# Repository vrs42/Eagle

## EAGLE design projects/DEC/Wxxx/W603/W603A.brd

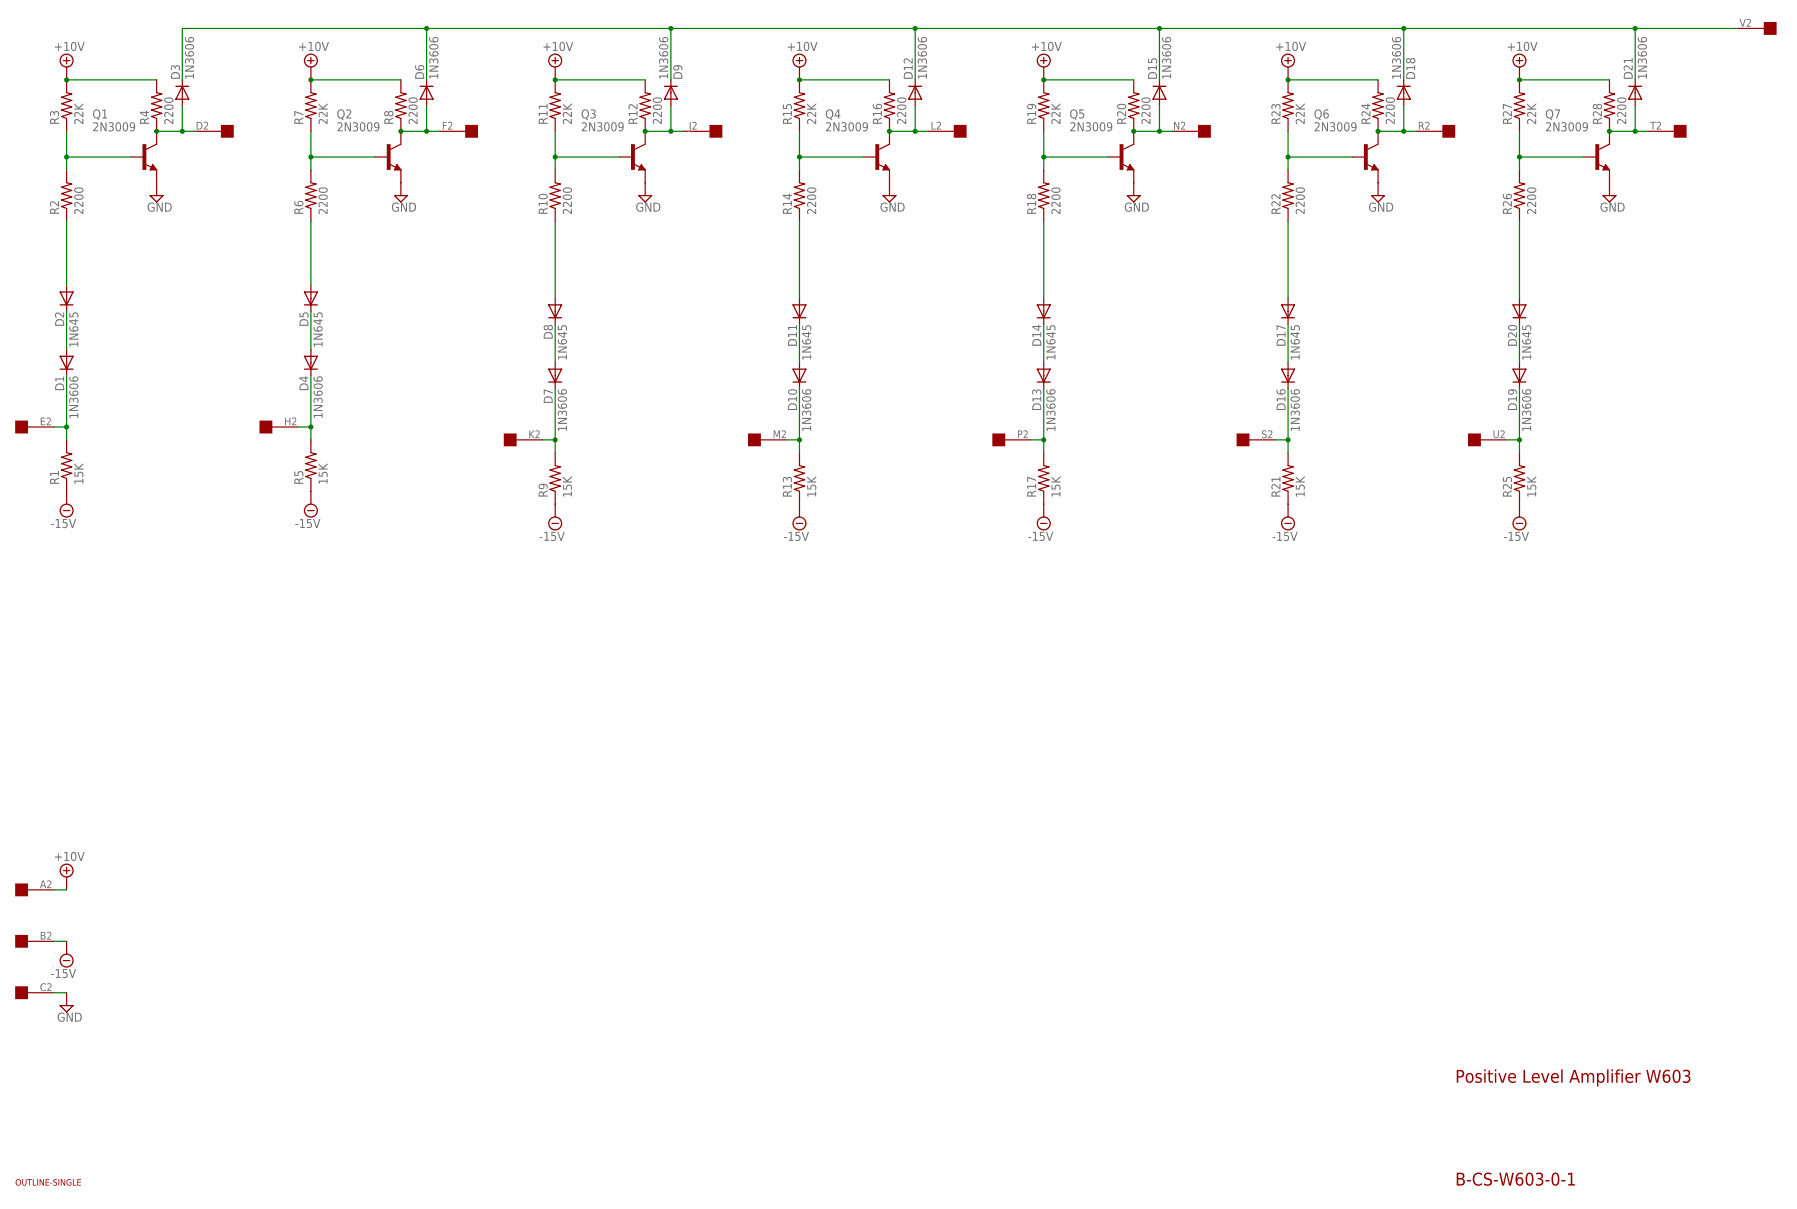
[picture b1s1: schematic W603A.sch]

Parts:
D1, D3, D4, D6, D7, D9, D10, D12, D13, D15, D16, D18, D19, D21: 1N3606; DO35-10
D2, D5, D8, D11, D14, D17, D20: 1N645; DO35-10
Q1, Q2, Q3, Q4, Q5, Q6, Q7: 2N3009; TO5
R1, R5, R9, R13, R17, R21, R25: 15K; 0207/10
R2, R4, R6, R8, R10, R12, R14, R16, R18, R20, R22, R24, R26, R28: 2200; 0207/10
R3, R7, R11, R15, R19, R23, R27: 22K; 0207/10
U$1: OUTLINE-SINGLE; SINGLE
U$2: EDGE-1; EDGE-CON1

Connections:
+10V: R3.2, R4.2, R7.2, R8.2, R11.2, R12.2, R15.2, R16.2, R19.2, R20.2, R23.2, R24.2, R27.2, R28.2, U$2.A2
-15V: R1.1, R5.1, R9.1, R13.1, R17.1, R21.1, R25.1, U$2.B2
GND: Q1.1 (E), Q2.1 (E), Q3.1 (E), Q4.1 (E), Q5.1 (E), Q6.1 (E), Q7.1 (E), U$2.C2
unnamed: D1.C, R1.2, U$2.E2
unnamed: D1.A, D2.C
unnamed: D2.A, R2.1
unnamed: Q1.2 (B), R2.2, R3.1
unnamed: D3.A, Q1.3 (C), R4.1, U$2.D2
unnamed: D4.C, R5.2, U$2.H2
unnamed: D4.A, D5.C
unnamed: D5.A, R6.1
unnamed: Q2.2 (B), R6.2, R7.1
unnamed: D6.A, Q2.3 (C), R8.1, U$2.F2
unnamed: D7.C, R9.2, U$2.K2
unnamed: D7.A, D8.C
unnamed: D8.A, R10.1
unnamed: Q3.2 (B), R10.2, R11.1
unnamed: D9.A, Q3.3 (C), R12.1, U$2.J2
unnamed: D3.C, D6.C, D9.C, D12.C, D15.C, D18.C, D21.C, U$2.V2
unnamed: D10.C, R13.2, U$2.M2
unnamed: D10.A, D11.C
unnamed: D11.A, R14.1
unnamed: Q4.2 (B), R14.2, R15.1
unnamed: D12.A, Q4.3 (C), R16.1, U$2.L2
unnamed: D13.C, R17.2, U$2.P2
unnamed: D13.A, D14.C
unnamed: D14.A, R18.1
unnamed: Q5.2 (B), R18.2, R19.1
unnamed: D15.A, Q5.3 (C), R20.1, U$2.N2
unnamed: D16.C, R21.2, U$2.S2
unnamed: D16.A, D17.C
unnamed: D17.A, R22.1
unnamed: Q6.2 (B), R22.2, R23.1
unnamed: D18.A, Q6.3 (C), R24.1, U$2.R2
unnamed: D19.C, R25.2, U$2.U2
unnamed: D19.A, D20.C
unnamed: D20.A, R26.1
unnamed: Q7.2 (B), R26.2, R27.1
unnamed: D21.A, Q7.3 (C), R28.1, U$2.T2

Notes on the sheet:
Positive Level Amplifier W603
B-CS-W603-0-1

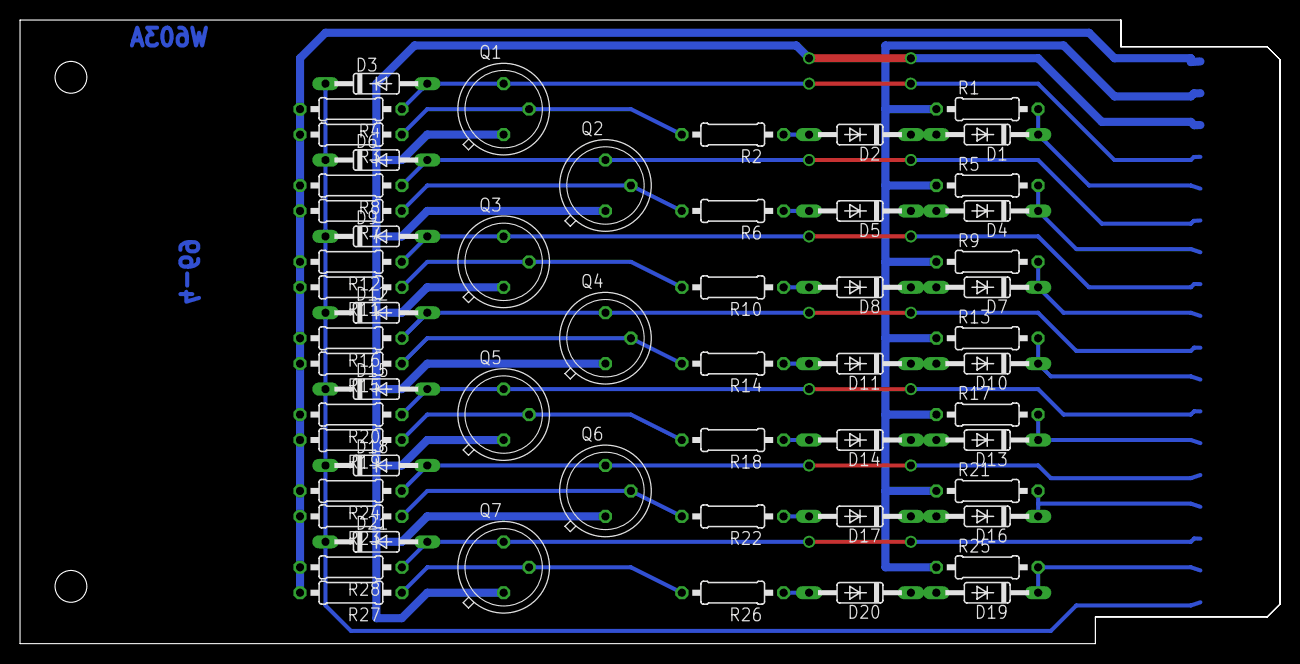
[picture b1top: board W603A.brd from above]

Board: 2 copper layers, 125.7 x 62.2 mm, 58 parts (0 on the bottom side), 39 nets.

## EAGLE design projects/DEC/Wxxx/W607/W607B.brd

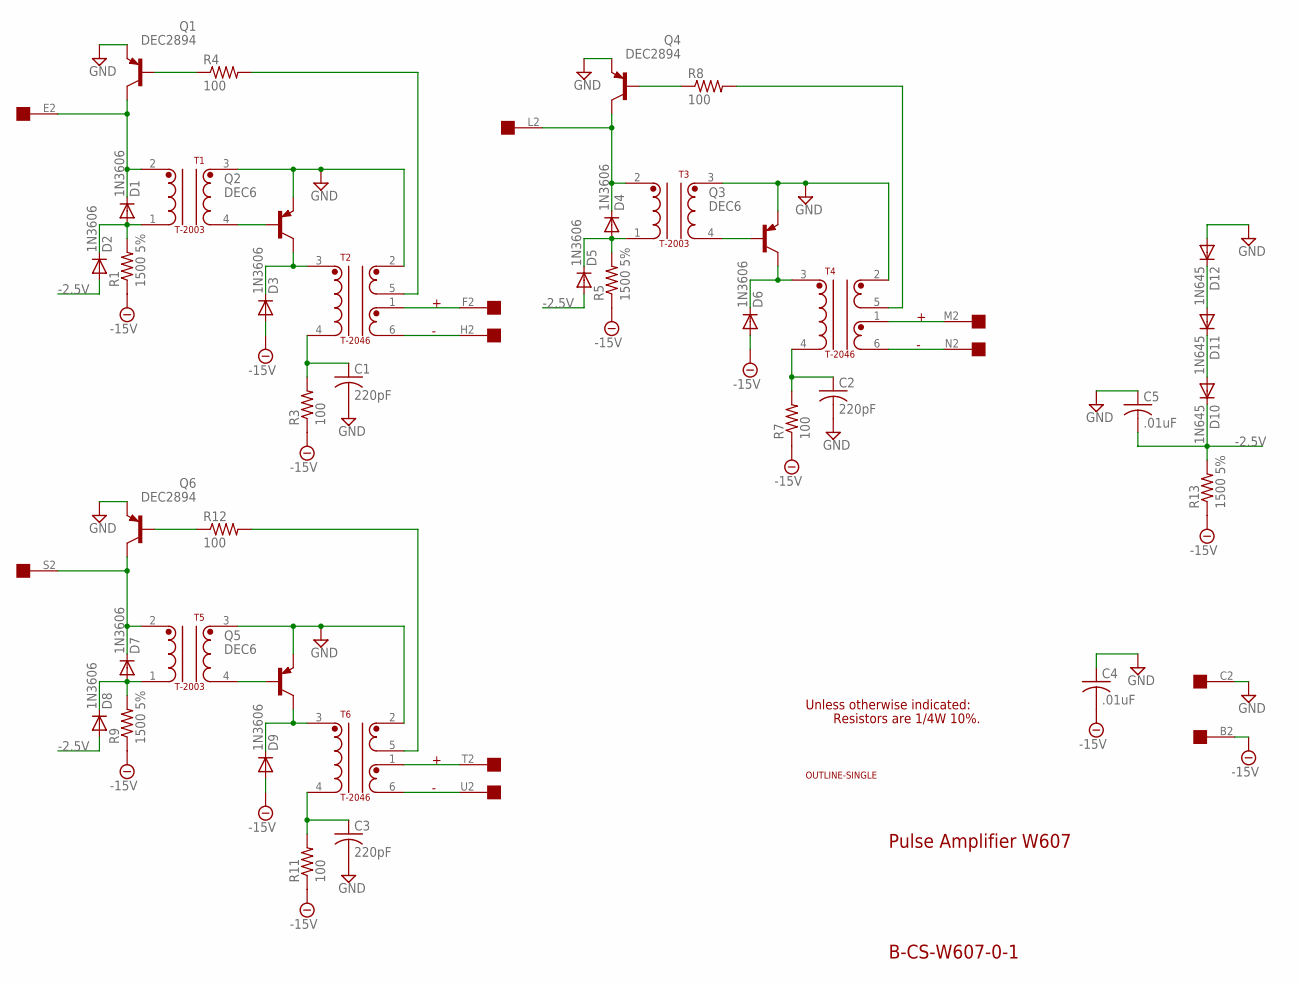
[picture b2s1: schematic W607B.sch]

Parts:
C1, C2, C3: 220pF; C050-025X075
C4, C5: .01uF; C050-025X075
D1, D2, D3, D4, D5, D6, D7, D8, D9: 1N3606; DO35-10
D10, D11, D12: 1N645; DO35-10
Q1, Q4, Q6: DEC2894; TO39
Q2, Q3, Q5: DEC6; TO39
R1, R5, R9, R13: 1500 5%; 0207/10
R3, R4, R7, R8, R11, R12: 100; 0207/10
T1, T3, T5: T-2003; TRANSFORMER2
T2, T4, T6: T-2046; TRANSFORMER6
U$1: OUTLINE-SINGLE; SINGLE
U$2: EDGE-1; EDGE-CON1

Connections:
-2.5V: C5.2, D2.A, D5.A, D8.A, D10.C, R13.2
-15V: C4.2, D3.A, D6.A, D9.A, R1.1, R3.1, R5.1, R7.1, R9.1, R11.1, R13.1, U$2.B2
GND: C1.2, C2.2, C3.2, C4.1, C5.1, D12.A, Q1.1 (E), Q2.1 (E), Q3.1 (E), Q4.1 (E), Q5.1 (E), Q6.1 (E), T1.3, T2.2, T3.3, T4.2, T5.3, T6.2, U$2.C2
unnamed: C1.1, R3.2, T2.4
unnamed: D1.C, Q1.3 (C), T1.2, U$2.E2
unnamed: D1.A, D2.C, R1.2, T1.1
unnamed: Q1.2 (B), R4.1
unnamed: Q2.2 (B), T1.4
unnamed: R4.2, T2.5
unnamed: D4.C, Q4.3 (C), T3.2, U$2.L2
unnamed: D4.A, D5.C, R5.2, T3.1
unnamed: T2.1, U$2.F2
unnamed: Q3.2 (B), T3.4
unnamed: T2.6, U$2.H2
unnamed: D3.C, Q2.3 (C), T2.3
unnamed: D6.C, Q3.3 (C), T4.3
unnamed: C2.1, R7.2, T4.4
unnamed: Q4.2 (B), R8.1
unnamed: R8.2, T4.5
unnamed: T4.1, U$2.M2
unnamed: T4.6, U$2.N2
unnamed: D7.C, Q6.3 (C), T5.2, U$2.S2
unnamed: D7.A, D8.C, R9.2, T5.1
unnamed: Q5.2 (B), T5.4
unnamed: D9.C, Q5.3 (C), T6.3
unnamed: C3.1, R11.2, T6.4
unnamed: Q6.2 (B), R12.1
unnamed: R12.2, T6.5
unnamed: T6.1, U$2.T2
unnamed: T6.6, U$2.U2
unnamed: D11.A, D12.C
unnamed: D10.A, D11.C

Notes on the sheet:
Pulse Amplifier W607
B-CS-W607-0-1
Unless otherwise indicated:
Resistors are 1/4W 10%.

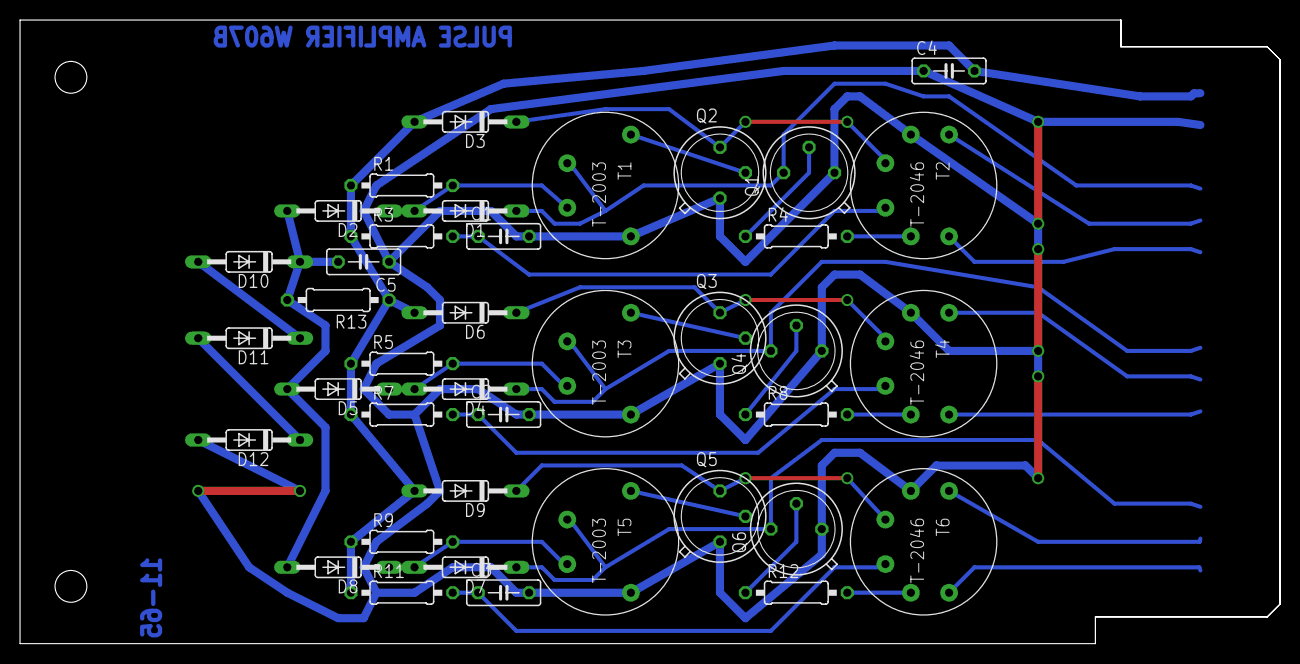
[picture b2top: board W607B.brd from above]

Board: 2 copper layers, 125.7 x 62.2 mm, 41 parts (0 on the bottom side), 32 nets.

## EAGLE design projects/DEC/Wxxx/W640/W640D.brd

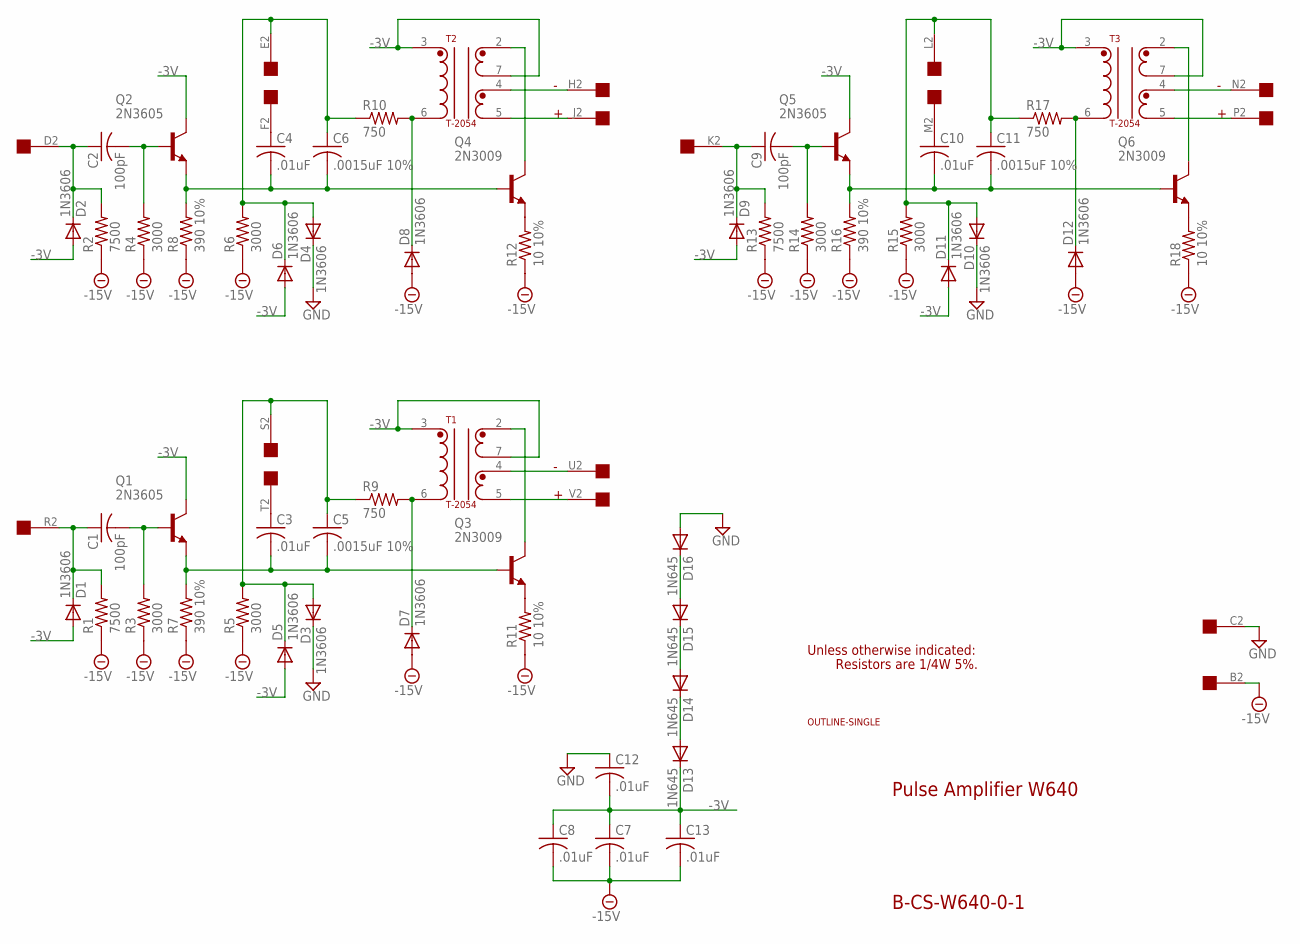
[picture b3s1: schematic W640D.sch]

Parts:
C1, C2, C9: 100pF; C050-025X075
C3, C4, C7, C8, C10, C12, C13: .01uF; C050-025X075
C5, C6, C11: .0015uF 10%; C050-025X075
D1, D2, D3, D4, D5, D6, D7, D8, D9, D10, D11, D12: 1N3606; DO35-10
D13, D14, D15, D16: 1N645; DO35-10
Q1, Q2, Q5: 2N3605; TO5
Q3, Q4, Q6: 2N3009; TO5
R1, R2, R13: 7500; 0207/10
R3, R4, R5, R6, R14, R15: 3000; 0207/10
R7, R8, R16: 390 10%; 0207/10
R9, R10, R17: 750; 0207/10
R11, R12, R18: 10 10%; 0207/10
T1, T2, T3: T-2054; TRANSFORMER6B
U$1: OUTLINE-SINGLE; SINGLE
U$2: EDGE-1; EDGE-CON1

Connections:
-3V: C7.1, C8.1, C12.2, C13.1, D1.A, D2.A, D5.A, D6.A, D9.A, D11.A, D13.C, Q1.3 (C), Q2.3 (C), Q5.3 (C), T1.3, T1.7 (5), T2.3, T2.7 (5), T3.3, T3.7 (5)
-15V: C7.2, C8.2, C13.2, D7.A, D8.A, D12.A, R1.1, R2.1, R3.1, R4.1, R5.1, R6.1, R7.1, R8.1, R11.1, R12.1, R13.1, R14.1, R15.1, R16.1, R18.1, U$2.B2
GND: C12.1, D3.C, D4.C, D10.C, D16.A, U$2.C2
unnamed: D8.C, R10.2, T2.6 (4)
unnamed: C2.1, D2.C, R2.2, U$2.D2
unnamed: C2.2, Q2.2 (B), R4.2
unnamed: C4.2, C6.2, Q2.1 (E), Q4.2 (B), R8.2
unnamed: C4.1, U$2.F2
unnamed: C6.1, D4.A, D6.C, R6.2, R10.1, U$2.E2
unnamed: Q4.3 (C), T2.2
unnamed: Q4.1 (E), R12.2
unnamed: T1.4 (1), U$2.U2
unnamed: T2.4 (1), U$2.H2
unnamed: T1.5 (6), U$2.V2
unnamed: T2.5 (6), U$2.J2
unnamed: D7.C, R9.2, T1.6 (4)
unnamed: C1.1, D1.C, R1.2, U$2.R2
unnamed: C1.2, Q1.2 (B), R3.2
unnamed: C3.2, C5.2, Q1.1 (E), Q3.2 (B), R7.2
unnamed: C3.1, U$2.T2
unnamed: C5.1, D3.A, D5.C, R5.2, R9.1, U$2.S2
unnamed: Q3.3 (C), T1.2
unnamed: Q3.1 (E), R11.2
unnamed: T3.4 (1), U$2.N2
unnamed: T3.5 (6), U$2.P2
unnamed: D12.C, R17.2, T3.6 (4)
unnamed: C9.1, D9.C, R13.2, U$2.K2
unnamed: C9.2, Q5.2 (B), R14.2
unnamed: C10.2, C11.2, Q5.1 (E), Q6.2 (B), R16.2
unnamed: C10.1, U$2.M2
unnamed: C11.1, D10.A, D11.C, R15.2, R17.1, U$2.L2
unnamed: Q6.3 (C), T3.2
unnamed: Q6.1 (E), R18.2
unnamed: D15.A, D16.C
unnamed: D13.A, D14.C
unnamed: D14.A, D15.C

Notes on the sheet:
Pulse Amplifier W640
B-CS-W640-0-1
Unless otherwise indicated:
Resistors are 1/4W 5%.

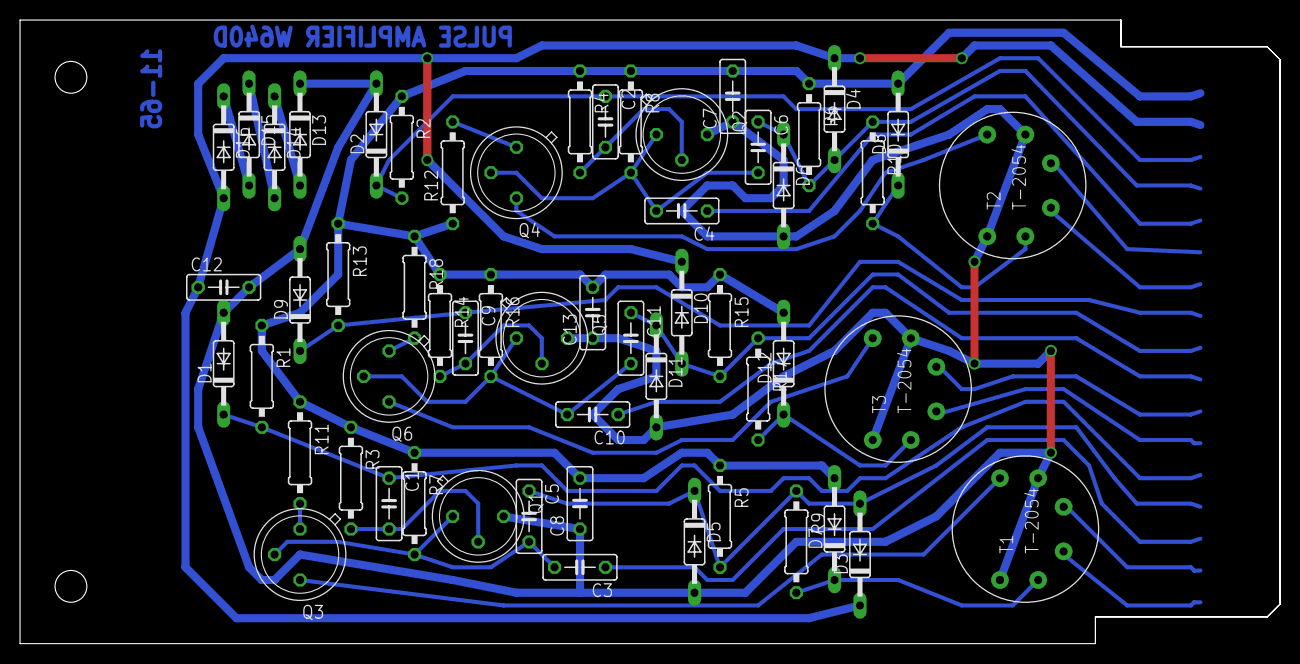
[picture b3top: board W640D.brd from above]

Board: 2 copper layers, 125.7 x 62.2 mm, 58 parts (0 on the bottom side), 36 nets.

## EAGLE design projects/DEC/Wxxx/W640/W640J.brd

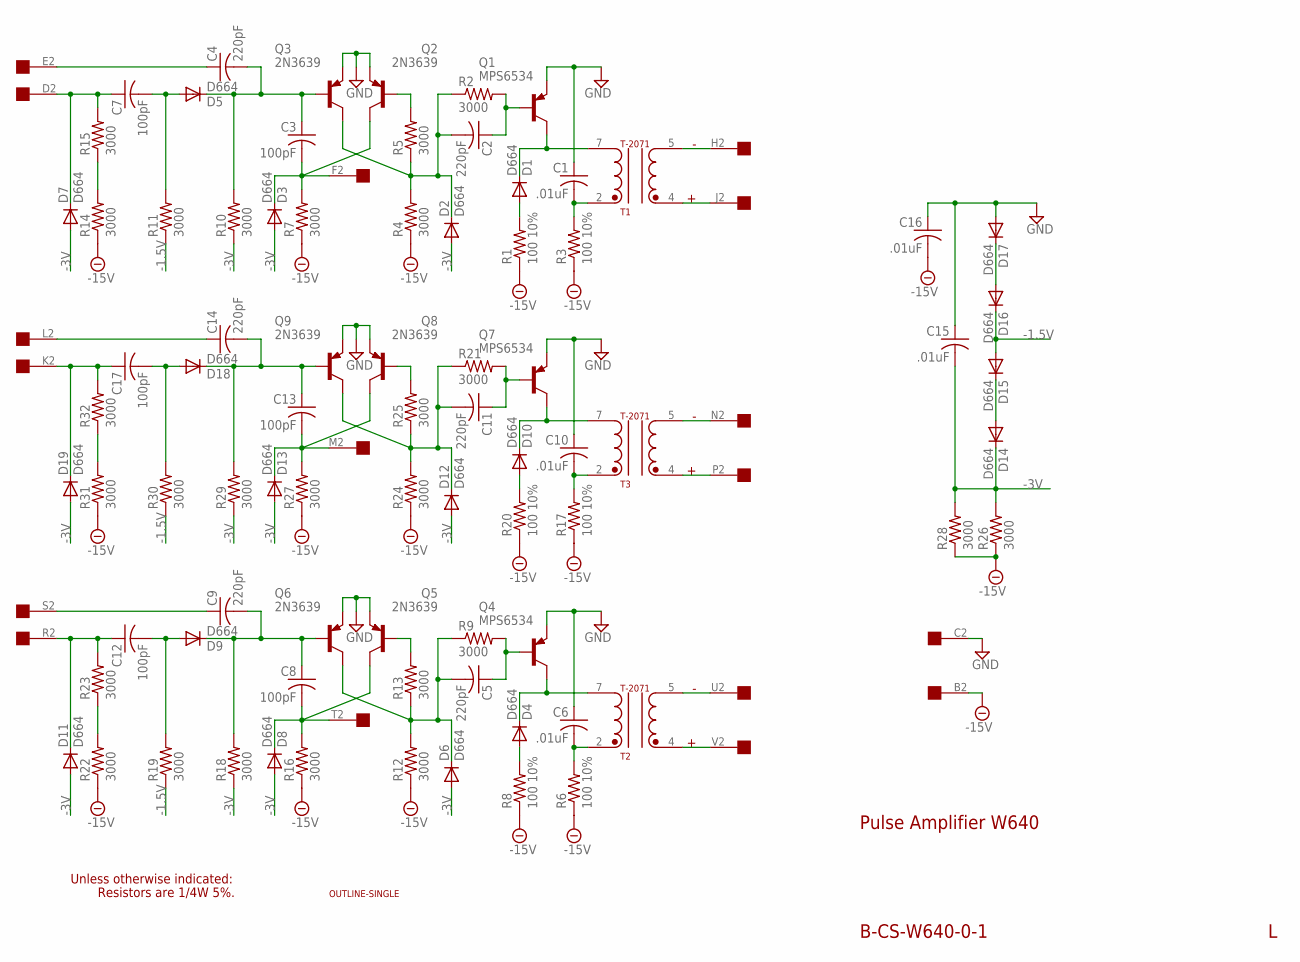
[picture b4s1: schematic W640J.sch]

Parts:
C1, C6, C10, C15, C16: .01uF; C063-025X075
C2, C4, C5, C9, C11, C14: 220pF; C063-025X075
C3, C7, C8, C12, C13, C17: 100pF; C063-025X075
D1, D2, D3, D4, D5, D6, D7, D8, D9, D10, D11, D12, D13, D14, D15, D16, D17, D18, D19: D664; DO35-10
Q1, Q4, Q7: MPS6534; TO5
Q2, Q3, Q5, Q6, Q8, Q9: 2N3639; TO5
R1, R3, R6, R8, R17, R20: 100 10%; 0207/10
R2, R4, R5, R7, R9, R10, R11, R12, R13, R14, R15, R16, R18, R19, R21, R22, R23, R24, R25, R26, R27, R28, R29, R30, R31, R32: 3000; 0207/10
T1, T2, T3: T-2071; TRANSFORMER
U$1: OUTLINE-SINGLE; SINGLE
U$2: EDGE-1; EDGE-CON1

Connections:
-1.5V: D15.A, D16.C, R11.1, R19.1, R30.1
-3V: C15.2, D2.A, D3.A, D6.A, D7.A, D8.A, D11.A, D12.A, D13.A, D14.C, D19.A, R10.1, R18.1, R26.2, R28.2, R29.1
-15V: C16.2, R1.1, R3.1, R4.1, R6.1, R7.1, R8.1, R12.1, R14.1, R16.1, R17.1, R20.1, R22.1, R24.1, R26.1, R27.1, R28.1, R31.1, U$2.B2
GND: C1.1, C6.1, C10.1, C15.1, C16.1, D17.A, Q1.1 (E), Q2.1 (E), Q3.1 (E), Q4.1 (E), Q5.1 (E), Q6.1 (E), Q7.1 (E), Q8.1 (E), Q9.1 (E), U$2.C2
unnamed: Q2.2 (B), R5.2
unnamed: T3.5, U$2.N2
unnamed: Q8.2 (B), R25.2
unnamed: Q5.2 (B), R13.2
unnamed: C3.1, C4.2, D5.C, Q3.2 (B), R10.2
unnamed: D1.C, Q1.3 (C), T1.7
unnamed: C1.2, R3.2, T1.2
unnamed: C4.1, U$2.E2
unnamed: T1.5, U$2.H2
unnamed: C7.2, D5.A, R11.2
unnamed: T1.4, U$2.J2
unnamed: C7.1, D7.C, R15.2, U$2.D2
unnamed: R14.2, R15.1
unnamed: T3.4, U$2.P2
unnamed: D10.C, Q7.3 (C), T3.7
unnamed: C10.2, R17.2, T3.2
unnamed: D10.A, R20.2
unnamed: C11.2, D12.C, Q9.3 (C), R21.1, R24.2, R25.1
unnamed: C11.1, Q7.2 (B), R21.2
unnamed: C13.2, D13.C, Q8.3 (C), R27.2, U$2.M2
unnamed: C13.1, C14.2, D18.C, Q9.2 (B), R29.2
unnamed: C14.1, U$2.L2
unnamed: C17.2, D18.A, R30.2
unnamed: C17.1, D19.C, R32.2, U$2.K2
unnamed: R31.2, R32.1
unnamed: T2.5, U$2.U2
unnamed: T2.4, U$2.V2
unnamed: D4.C, Q4.3 (C), T2.7
unnamed: D16.A, D17.C
unnamed: D14.A, D15.C
unnamed: C6.2, R6.2, T2.2
unnamed: D1.A, R1.2
unnamed: C2.2, D2.C, Q3.3 (C), R2.1, R4.2, R5.1
unnamed: C2.1, Q1.2 (B), R2.2
unnamed: D4.A, R8.2
unnamed: C3.2, D3.C, Q2.3 (C), R7.2, U$2.F2
unnamed: C5.2, D6.C, Q6.3 (C), R9.1, R12.2, R13.1
unnamed: C5.1, Q4.2 (B), R9.2
unnamed: C8.2, D8.C, Q5.3 (C), R16.2, U$2.T2
unnamed: C8.1, C9.2, D9.C, Q6.2 (B), R18.2
unnamed: C9.1, U$2.S2
unnamed: C12.2, D9.A, R19.2
unnamed: C12.1, D11.C, R23.2, U$2.R2
unnamed: R22.2, R23.1

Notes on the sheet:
Pulse Amplifier W640
B-CS-W640-0-1
Unless otherwise indicated:
Resistors are 1/4W 5%.

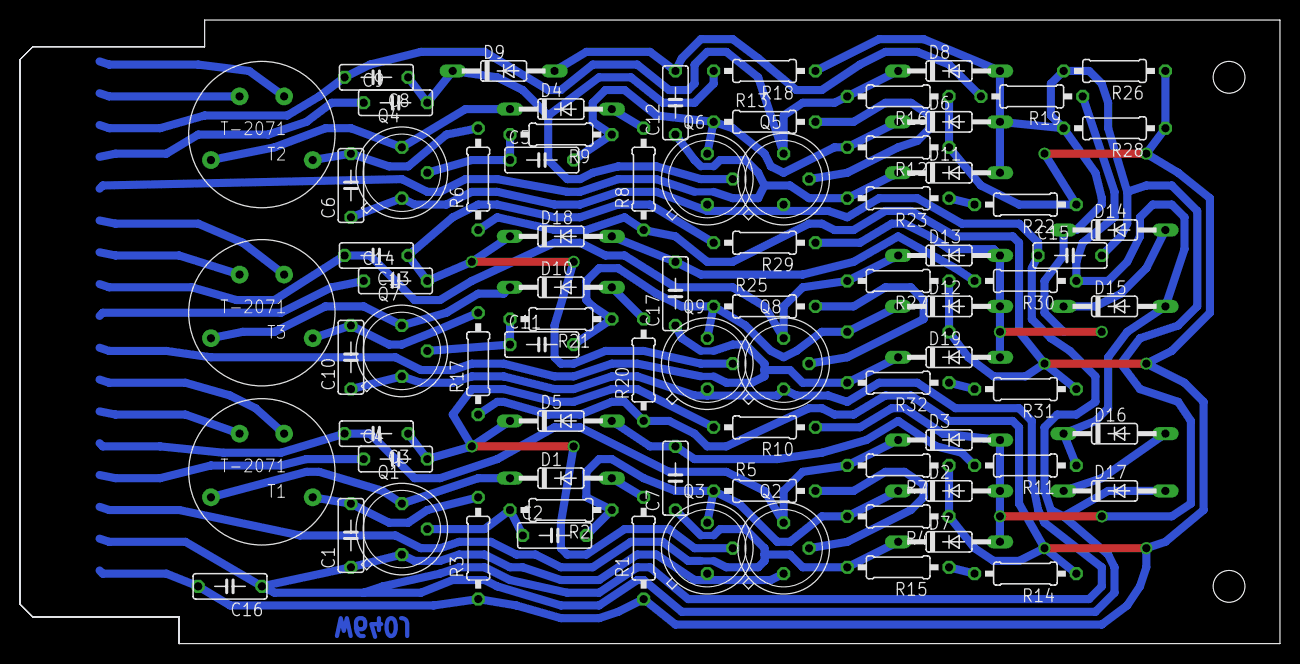
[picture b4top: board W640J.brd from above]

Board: 2 copper layers, 125.7 x 62.2 mm, 82 parts (1 on the bottom side), 48 nets.

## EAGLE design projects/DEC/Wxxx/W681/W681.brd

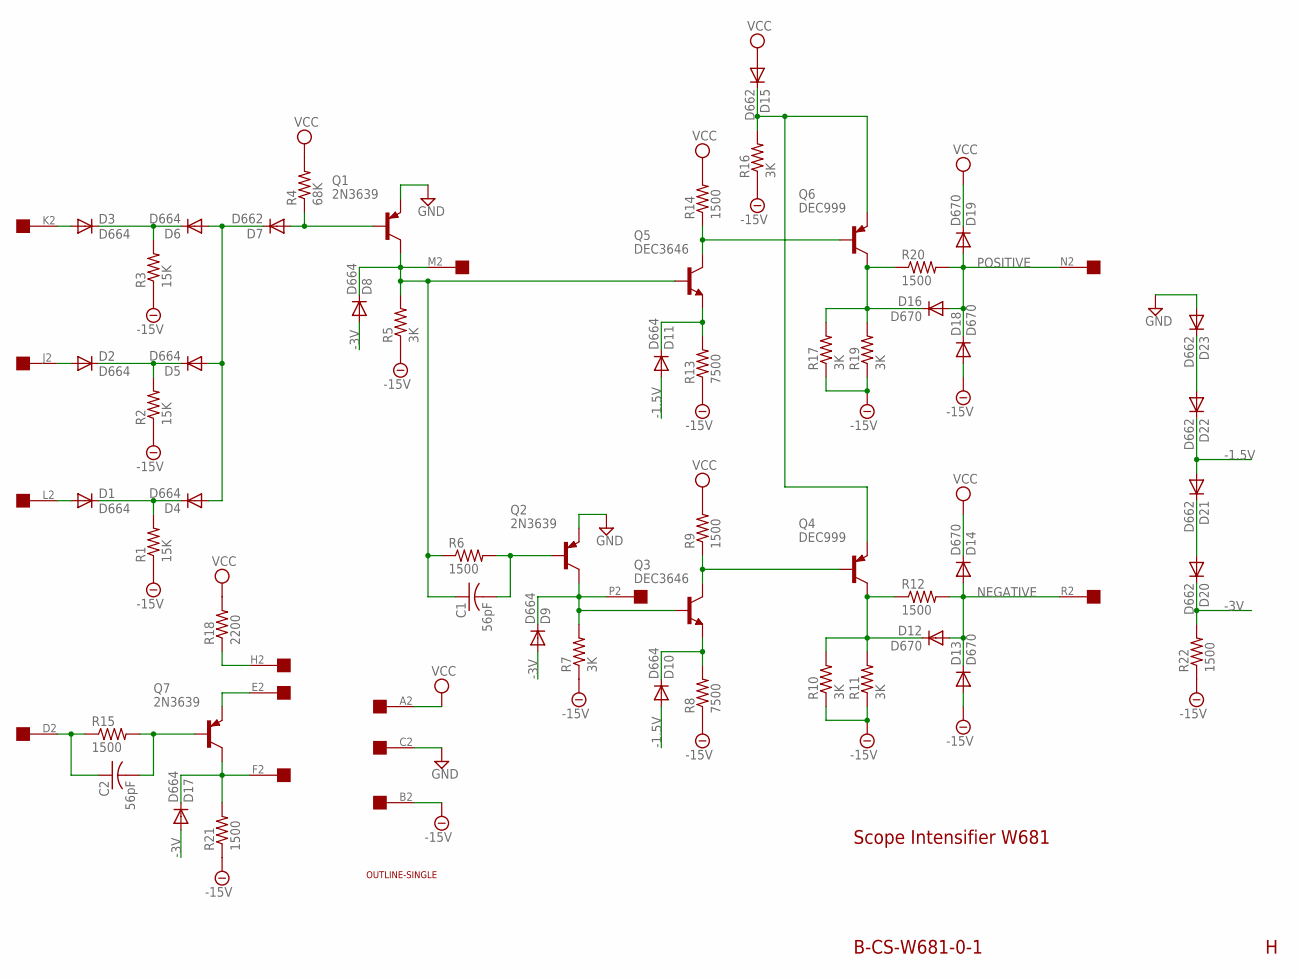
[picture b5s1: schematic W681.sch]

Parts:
C1, C2: 56pF; C063-025X075
D1, D2, D3, D4, D5, D6, D8, D9, D10, D11, D17: D664; DO35-10
D7, D15, D20, D21, D22, D23: D662; DO35-10
D12, D13, D14, D16, D18, D19: D670; DO35-10
Q1, Q2, Q7: 2N3639; TO5
Q3, Q5: DEC3646; TO5
Q4, Q6: DEC999; TO5
R1, R2, R3: 15K; 0207/10
R4: 68K; 0207/10
R5, R7, R10, R11, R16, R17, R19: 3K; 0207/10
R6, R9, R12, R14, R15, R20, R21, R22: 1500; 0207/10
R8, R13: 7500; 0207/10
R18: 2200; 0207/10
U$1: OUTLINE-SINGLE; SINGLE
U$2: EDGE-1; EDGE-CON1

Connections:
-1.5V: D10.A, D11.A, D21.A, D22.C
-3V: D8.A, D9.A, D17.A, D20.C, R22.2
-15V: D13.A, D18.A, R1.1, R2.1, R3.1, R5.1, R7.1, R8.1, R10.1, R11.1, R13.1, R16.1, R17.1, R19.1, R21.1, R22.1, U$2.B2
GND: D23.A, Q1.1 (E), Q2.1 (E), U$2.C2
unnamed: D1.A, U$2.L2
unnamed: D2.A, U$2.J2
unnamed: D3.A, U$2.K2
unnamed: D1.C, D4.C, R1.2
unnamed: D2.C, D5.C, R2.2
unnamed: D3.C, D6.C, R3.2
unnamed: D4.A, D5.A, D6.A, D7.C
unnamed: D7.A, Q1.2 (B), R4.1
unnamed: C1.1, D8.C, Q1.3 (C), Q5.2 (B), R5.2, R6.1, U$2.M2
unnamed: C1.2, Q2.2 (B), R6.2
unnamed: D9.C, Q2.3 (C), Q3.2 (B), R7.2, U$2.P2
unnamed: Q3.3 (C), Q4.2 (B), R9.1
unnamed: D10.C, Q3.1 (E), R8.2
unnamed: D12.C, Q4.3 (C), R10.2, R11.2, R12.1
unnamed: Q5.3 (C), Q6.2 (B), R14.1
unnamed: D11.C, Q5.1 (E), R13.2
unnamed: D15.C, Q4.1 (E), Q6.1 (E), R16.2
unnamed: D16.C, Q6.3 (C), R17.2, R19.2, R20.1
unnamed: C2.1, R15.1, U$2.D2
unnamed: C2.2, Q7.2 (B), R15.2
unnamed: D17.C, Q7.3 (C), R21.2, U$2.F2
unnamed: Q7.1 (E), U$2.E2
unnamed: R18.1, U$2.H2
unnamed: D20.A, D21.C
unnamed: D22.A, D23.C
NEGATIVE: D12.A, D13.C, D14.A, R12.2, U$2.R2
POSITIVE: D16.A, D18.C, D19.A, R20.2, U$2.N2
VCC: D14.C, D15.A, D19.C, R4.2, R9.2, R14.2, R18.2, U$2.A2

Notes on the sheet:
Scope Intensifier W681
B-CS-W681-0-1

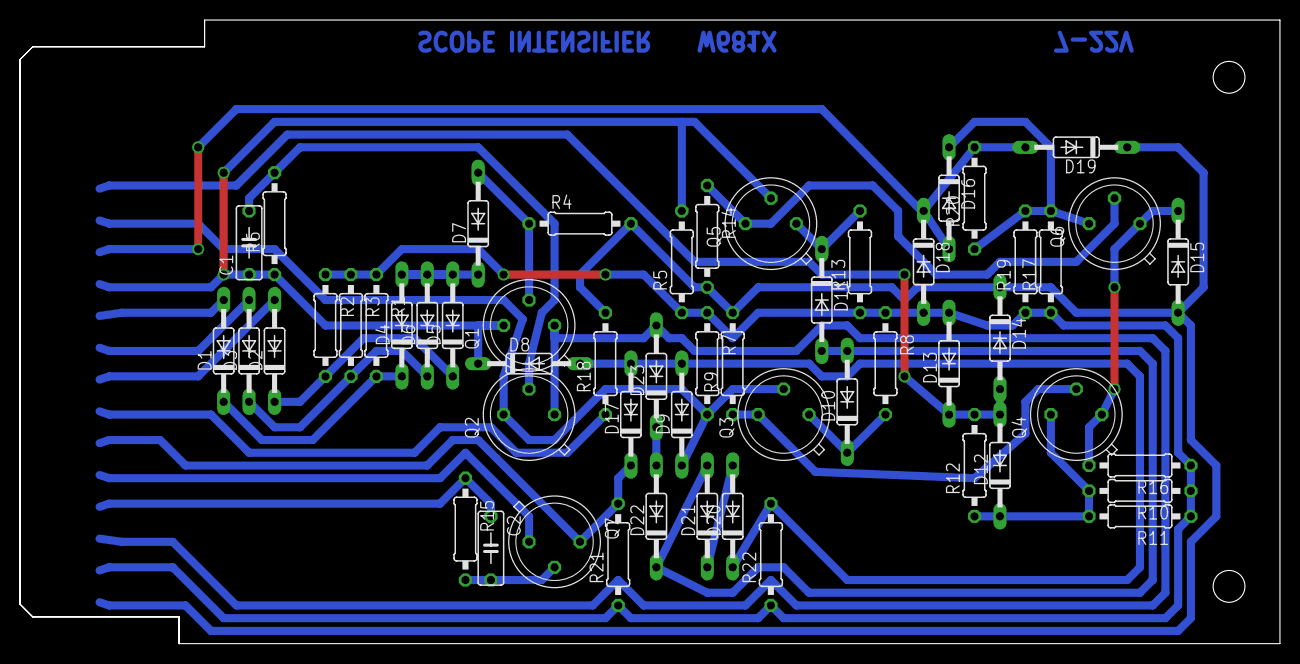
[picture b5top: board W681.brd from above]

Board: 2 copper layers, 125.7 x 62.2 mm, 56 parts (0 on the bottom side), 32 nets.

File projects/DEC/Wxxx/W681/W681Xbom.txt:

Partlist exported from C:/Users/Vince/Documents/eagle/projects/DEC/Wxxx/W681/W681X.sch at 7/22/2017 2:01:49 PM

Qty Value          Device         Package      Parts                                         Description                                 
8   1500           R-US_0207/10   0207/10      R6, R9, R12, R14, R15, R20, R21, R22          RESISTOR, American symbol                   
3   15K            R-US_0207/10   0207/10      R1, R2, R3                                    RESISTOR, American symbol                   
11  1N4150         DIODE-DO35-10  DO35-10      D1, D2, D3, D4, D5, D6, D8, D9, D10, D11, D17 DIODE                                       
6   1N914          DIODE-DO35-10  DO35-10      D7, D15, D20, D21, D22, D23                   DIODE                                       
6   1N914V         DIODE-DO35-10  DO35-10      D12, D13, D14, D16, D18, D19                  DIODE                                       
1   2200           R-US_0207/10   0207/10      R18                                           RESISTOR, American symbol                   
2   2N3906         -PNP-TO5       TO5          Q4, Q6                                        PNP Transistror                             
7   3K             R-US_0207/10   0207/10      R5, R7, R10, R11, R16, R17, R19               RESISTOR, American symbol                   
2   56pF           C-US           C063-025X075 C1, C2                                        Capacitors with funky DEC lead spacing.     
1   68K            R-US_0207/10   0207/10      R4                                            RESISTOR, American symbol                   
2   7500           R-US_0207/10   0207/10      R8, R13                                       RESISTOR, American symbol                   
1   OUTLINE-SINGLE OUTLINE-SINGLE SINGLE       U$1                                           W681 Board.              
2   PN3646         -NPN-TO5       TO5          Q3, Q5                                        NPN Transistror                             
3   PN4917         -PNP-TO5       TO5          Q1, Q2, Q7                                    PNP Transistror
